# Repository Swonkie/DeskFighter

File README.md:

# DeskFighter

These are the files used to design and build the DeskFighter keyboard.

There is an article which describes the process:

https://haldimann.app/DeskFighter/

## Organization

### 3D Printed Parts

Files in step and 3mf format to 3D print keycaps and other small parts required for the keyboard build.

### FreeCAD

FreeCAD files used to export the 3D printed parts above. If you want to make modifications, this is the most convenient option.

https://www.freecad.org/

### Keycaps Labels

Affinity and svg files used to design the labels. These were imported into FreeCAD.

### Matrix Layout

Spreadsheet used to plan the keyboard matrix layout.

### PCB

KiCad project files used to design the printed circuit board (PCB). The actual manufacturing files (gerber and drill files) are not included, but can be exported from KiCad. Those are then sent to a PCB manufacturer which will make the board.

Also includes the MacroPad files — a test project to figure out some things with a small PCB before ordering the large DeskFighter PCB.

https://www.kicad.org/

## Additional parts required

The mentioned shops are just suggestions. All parts are available in other shops too.

| Shop                                         | Item                                                                                 | Quantity |
| -------------------------------------------- | ------------------------------------------------------------------------------------ | -------: |
| [Keebart](https://www.keebart.com/)          | Switches (Kailh Choc V2 with 2 pins)                                                 |      100 |
|                                              | THT keycaps blank                                                                    |       60 |
|                                              | THT keycaps with dot                                                                 |        2 |
|                                              | THT keycaps with tactile marker                                                      |        2 |
| [Max Gaming](https://www.maxgaming.com/shop) | Durock V3 plate-mounted stabilizer set                                               |        1 |
| [DigiKey](https://www.digikey.com/)          | [Various electronics components](https://www.digikey.com/en/mylists/list/9PG9QW3RYC) |        – |
| [CNC Kitchen](https://cnckitchen.store/)     | M2 heat-set inserts                                                                  |       20 |
|                                              | Installation tip set (optional)                                                      |        1 |
| [AliExpress](https://www.aliexpress.com/)    | M2 × 5 mm screws, black, Torx                                                        |       10 |
|                                              | Rubber feet, 8 mm × 3 mm, self-adhesive                                              |       20 |

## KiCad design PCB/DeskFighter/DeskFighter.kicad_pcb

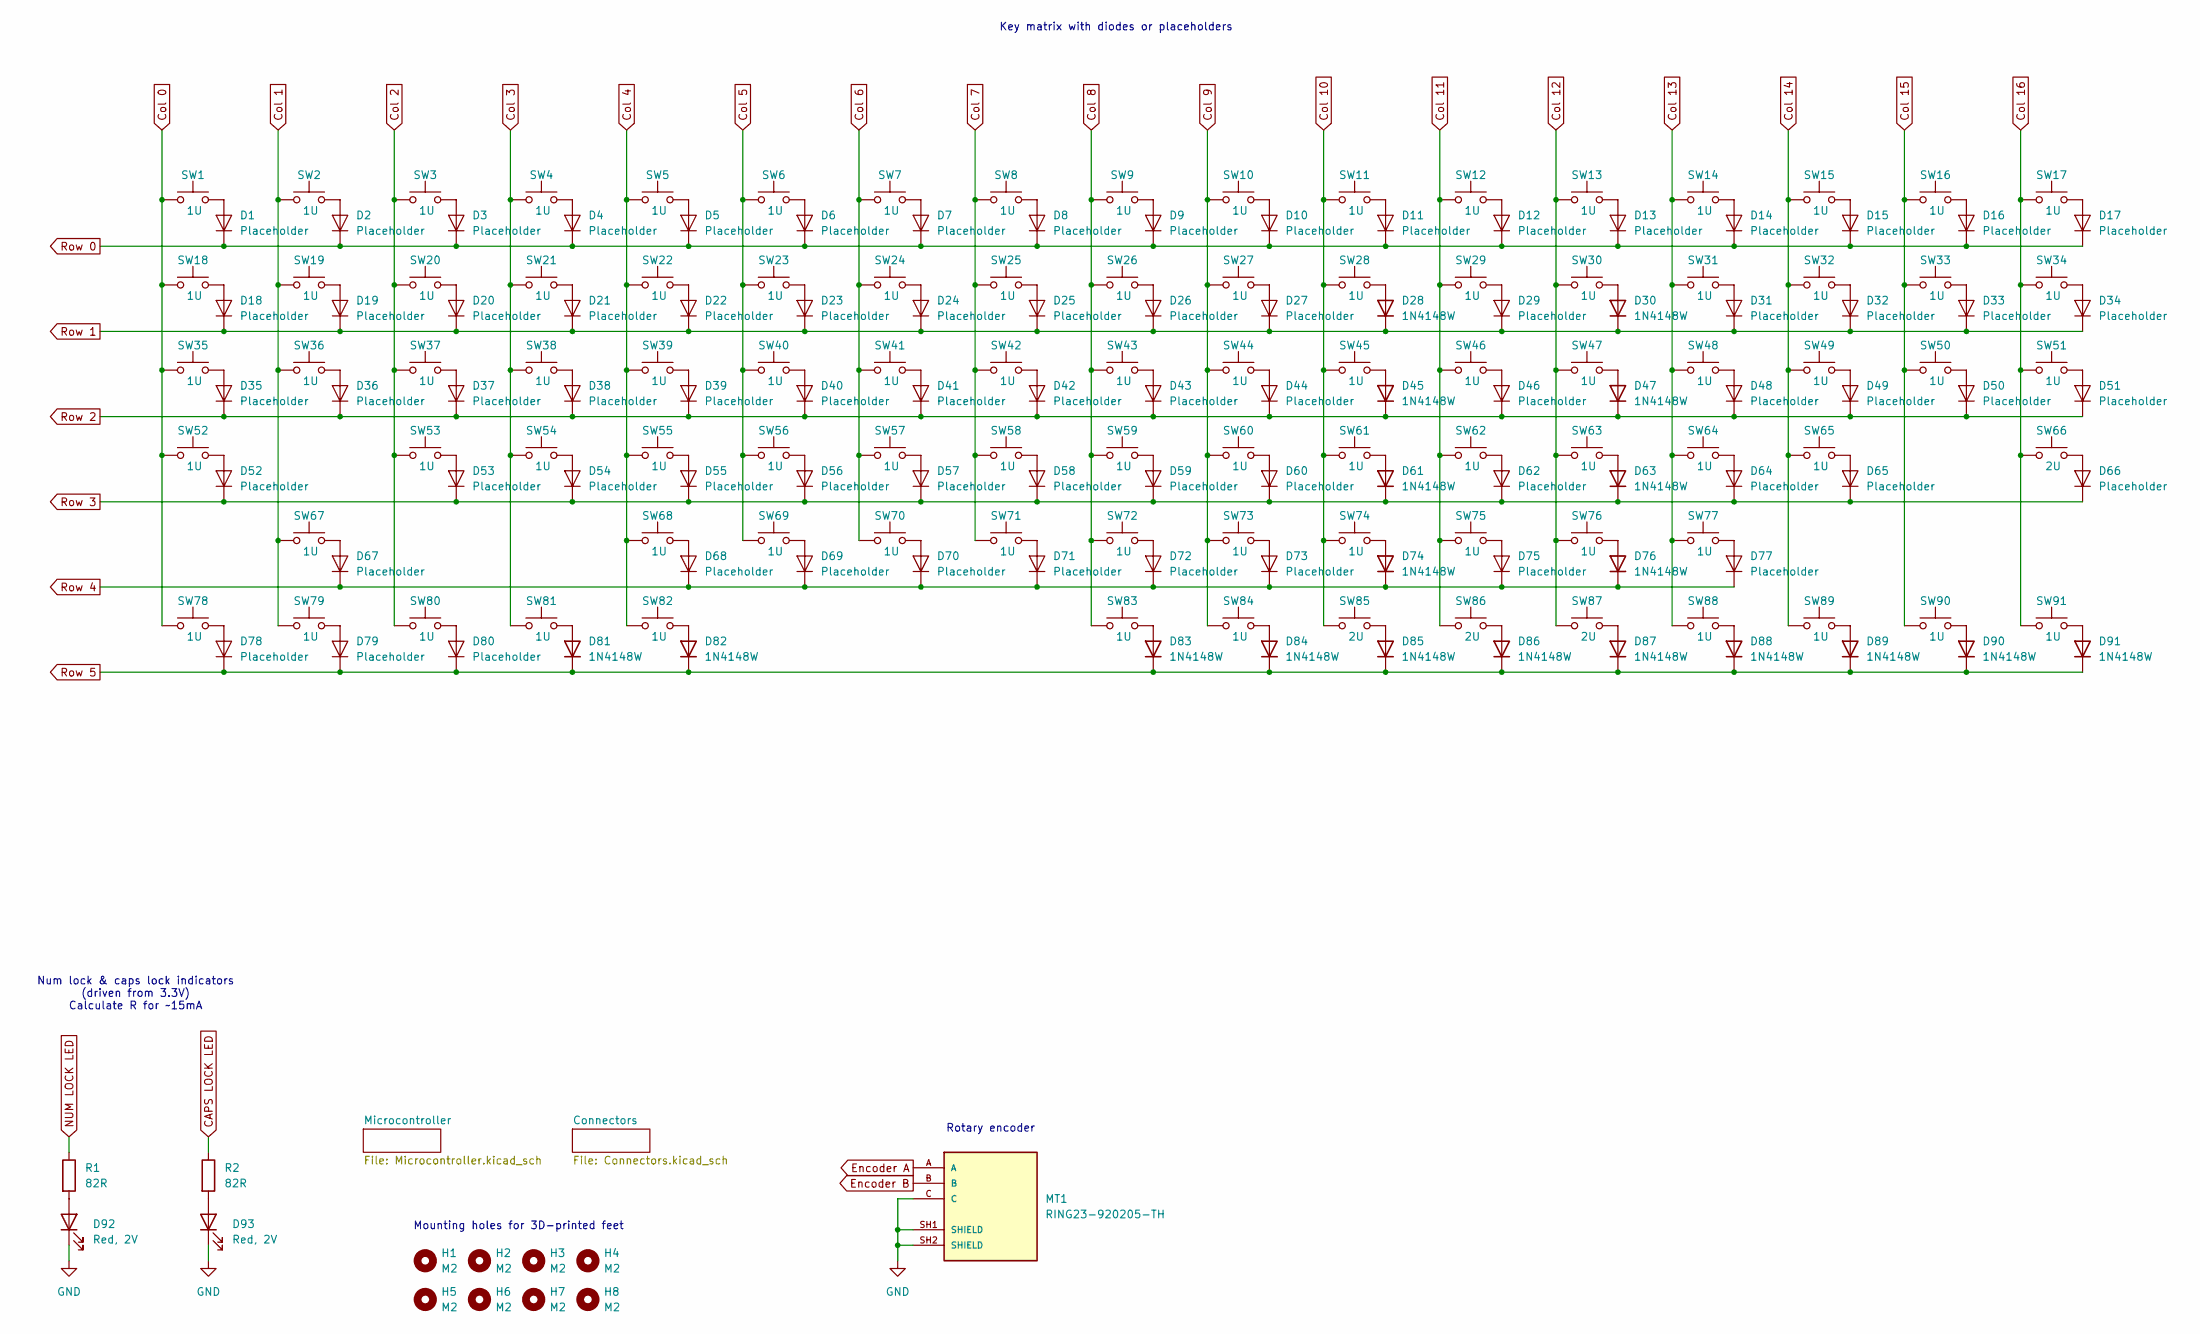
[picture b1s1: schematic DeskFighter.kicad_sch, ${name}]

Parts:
D1, D2, D3, D4, D5, D6, D7, D8, D9, D10, D11, D12, D13, D14, D15, D16, D17, D18, D19, D20, D21, D22, D23, D24, D25, D26, D27, D29, D31, D32, D33, D34, D35, D36, D37, D38, D39, D40, D41, D42, D43, D44, D46, D48, D49, D50, D51, D52, D53, D54, D55, D56, D57, D58, D59, D60, D62, D64, D65, D66, D67, D68, D69, D70, D71, D72, D73, D75, D77, D78, D79, D80: Placeholder; DiodePlaceholder
D28, D30, D45, D47, D61, D63, D74, D76, D81, D82, D83, D84, D85, D86, D87, D88, D89, D90, D91: 1N4148W; D_SOD-123_Handsolder
D92, D93: Red, 2V; LED_0805_2012Metric_Pad1.15x1.40mm_HandSolder
H1, H2, H3, H4, H5, H6, H7, H8: M2; MountingHole_2.2mm_M2_ISO14580_Pad_10mm_Standoffs
MT1: RING23-920205-TH; PARTREV 1.0
R1, R2: 82R; R_0805_2012Metric_Pad1.20x1.40mm_HandSolder
SW1, SW2, SW3, SW4, SW5, SW6, SW7, SW8, SW9, SW10, SW11, SW12, SW13, SW14, SW15, SW16, SW17, SW18, SW19, SW20, SW21, SW22, SW23, SW24, SW25, SW26, SW27, SW28, SW29, SW30, SW31, SW32, SW33, SW34, SW35, SW36, SW37, SW38, SW39, SW40, SW41, SW42, SW43, SW44, SW45, SW46, SW47, SW48, SW49, SW50, SW51, SW52, SW53, SW54, SW55, SW56, SW57, SW58, SW59, SW60, SW61, SW62, SW63, SW64, SW65, SW67, SW68, SW69, SW70, SW71, SW72, SW73, SW74, SW75, SW76, SW77, SW78, SW79, SW80, SW81, SW82, SW83, SW84, SW88, SW89, SW90, SW91: 1U; SW_Kailh_Choc_V2_1.00u
SW66, SW85, SW86, SW87: 2U; SW_Kailh_Choc_V2_2.00u

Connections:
CAPS LOCK LED: R2.1; also elsewhere on the board
Col 0: SW1.1, SW18.1, SW35.1, SW52.1, SW78.1; also elsewhere on the board
Col 1: SW2.1, SW19.1, SW36.1, SW67.1, SW79.1; also elsewhere on the board
Col 2: SW3.1, SW20.1, SW37.1, SW53.1, SW80.1; also elsewhere on the board
Col 3: SW4.1, SW21.1, SW38.1, SW54.1, SW81.1; also elsewhere on the board
Col 4: SW5.1, SW22.1, SW39.1, SW55.1, SW68.1, SW82.1; also elsewhere on the board
Col 5: SW6.1, SW23.1, SW40.1, SW56.1, SW69.1; also elsewhere on the board
Col 6: SW7.1, SW24.1, SW41.1, SW57.1, SW70.1; also elsewhere on the board
Col 7: SW8.1, SW25.1, SW42.1, SW58.1, SW71.1; also elsewhere on the board
Col 8: SW9.1, SW26.1, SW43.1, SW59.1, SW72.1, SW83.1; also elsewhere on the board
Col 9: SW10.1, SW27.1, SW44.1, SW60.1, SW73.1, SW84.1; also elsewhere on the board
Col 10: SW11.1, SW28.1, SW45.1, SW61.1, SW74.1, SW85.1; also elsewhere on the board
Col 11: SW12.1, SW29.1, SW46.1, SW62.1, SW75.1, SW86.1; also elsewhere on the board
Col 12: SW13.1, SW30.1, SW47.1, SW63.1, SW76.1, SW87.1; also elsewhere on the board
Col 13: SW14.1, SW31.1, SW48.1, SW64.1, SW77.1, SW88.1; also elsewhere on the board
Col 14: SW15.1, SW32.1, SW49.1, SW65.1, SW89.1; also elsewhere on the board
Col 15: SW16.1, SW33.1, SW50.1, SW90.1; also elsewhere on the board
Col 16: SW17.1, SW34.1, SW51.1, SW66.1, SW91.1; also elsewhere on the board
Encoder A: MT1.A; also elsewhere on the board
Encoder B: MT1.B; also elsewhere on the board
GND: D92.1 (K), D93.1 (K), MT1.C, MT1.SH1 (SHIELD), MT1.SH2 (SHIELD); also elsewhere on the board
NUM LOCK LED: R1.1; also elsewhere on the board
unnamed: D1.2 (A), SW1.2
unnamed: D2.2 (A), SW2.2
unnamed: D3.2 (A), SW3.2
unnamed: D4.2 (A), SW4.2
unnamed: D5.2 (A), SW5.2
unnamed: D6.2 (A), SW6.2
unnamed: D7.2 (A), SW7.2
unnamed: D8.2 (A), SW8.2
unnamed: D9.2 (A), SW9.2
unnamed: D10.2 (A), SW10.2
unnamed: D11.2 (A), SW11.2
unnamed: D12.2 (A), SW12.2
unnamed: D13.2 (A), SW13.2
unnamed: D14.2 (A), SW14.2
unnamed: D15.2 (A), SW15.2
unnamed: D16.2 (A), SW16.2
unnamed: D17.2 (A), SW17.2
unnamed: D18.2 (A), SW18.2
unnamed: D19.2 (A), SW19.2
unnamed: D20.2 (A), SW20.2
unnamed: D21.2 (A), SW21.2
unnamed: D22.2 (A), SW22.2
unnamed: D23.2 (A), SW23.2
unnamed: D24.2 (A), SW24.2
unnamed: D25.2 (A), SW25.2
unnamed: D26.2 (A), SW26.2
unnamed: D27.2 (A), SW27.2
unnamed: D28.2 (A), SW28.2
unnamed: D29.2 (A), SW29.2
unnamed: D30.2 (A), SW30.2
unnamed: D31.2 (A), SW31.2
unnamed: D32.2 (A), SW32.2
unnamed: D33.2 (A), SW33.2
unnamed: D34.2 (A), SW34.2
unnamed: D35.2 (A), SW35.2
unnamed: D36.2 (A), SW36.2
unnamed: D37.2 (A), SW37.2
unnamed: D38.2 (A), SW38.2
unnamed: D39.2 (A), SW39.2
unnamed: D40.2 (A), SW40.2
unnamed: D41.2 (A), SW41.2
unnamed: D42.2 (A), SW42.2
unnamed: D43.2 (A), SW43.2
unnamed: D44.2 (A), SW44.2
unnamed: D45.2 (A), SW45.2
unnamed: D46.2 (A), SW46.2
unnamed: D47.2 (A), SW47.2
unnamed: D48.2 (A), SW48.2
unnamed: D49.2 (A), SW49.2
unnamed: D50.2 (A), SW50.2
unnamed: D51.2 (A), SW51.2
unnamed: D52.2 (A), SW52.2
unnamed: D53.2 (A), SW53.2
unnamed: D54.2 (A), SW54.2
unnamed: D55.2 (A), SW55.2
unnamed: D56.2 (A), SW56.2
unnamed: D57.2 (A), SW57.2
unnamed: D58.2 (A), SW58.2
unnamed: D59.2 (A), SW59.2
unnamed: D60.2 (A), SW60.2
unnamed: D61.2 (A), SW61.2
unnamed: D62.2 (A), SW62.2
unnamed: D63.2 (A), SW63.2
unnamed: D64.2 (A), SW64.2
unnamed: D65.2 (A), SW65.2
unnamed: D66.2 (A), SW66.2
unnamed: D67.2 (A), SW67.2
unnamed: D68.2 (A), SW68.2
unnamed: D69.2 (A), SW69.2
unnamed: D70.2 (A), SW70.2
unnamed: D71.2 (A), SW71.2
unnamed: D72.2 (A), SW72.2
unnamed: D73.2 (A), SW73.2
unnamed: D74.2 (A), SW74.2
unnamed: D75.2 (A), SW75.2
unnamed: D76.2 (A), SW76.2
unnamed: D77.2 (A), SW77.2
unnamed: D78.2 (A), SW78.2
unnamed: D79.2 (A), SW79.2
unnamed: D80.2 (A), SW80.2
unnamed: D81.2 (A), SW81.2
unnamed: D82.2 (A), SW82.2
unnamed: D83.2 (A), SW83.2
unnamed: D84.2 (A), SW84.2
unnamed: D85.2 (A), SW85.2
unnamed: D86.2 (A), SW86.2
unnamed: D87.2 (A), SW87.2
unnamed: D88.2 (A), SW88.2
unnamed: D89.2 (A), SW89.2
unnamed: D90.2 (A), SW90.2
unnamed: D91.2 (A), SW91.2
unnamed: D92.2 (A), R1.2
unnamed: D93.2 (A), R2.2
Row 0: D1.1 (K), D2.1 (K), D3.1 (K), D4.1 (K), D5.1 (K), D6.1 (K), D7.1 (K), D8.1 (K), D9.1 (K), D10.1 (K), D11.1 (K), D12.1 (K), D13.1 (K), D14.1 (K), D15.1 (K), D16.1 (K), D17.1 (K); also elsewhere on the board
Row 1: D18.1 (K), D19.1 (K), D20.1 (K), D21.1 (K), D22.1 (K), D23.1 (K), D24.1 (K), D25.1 (K), D26.1 (K), D27.1 (K), D28.1 (K), D29.1 (K), D30.1 (K), D31.1 (K), D32.1 (K), D33.1 (K), D34.1 (K); also elsewhere on the board
Row 2: D35.1 (K), D36.1 (K), D37.1 (K), D38.1 (K), D39.1 (K), D40.1 (K), D41.1 (K), D42.1 (K), D43.1 (K), D44.1 (K), D45.1 (K), D46.1 (K), D47.1 (K), D48.1 (K), D49.1 (K), D50.1 (K), D51.1 (K); also elsewhere on the board
Row 3: D52.1 (K), D53.1 (K), D54.1 (K), D55.1 (K), D56.1 (K), D57.1 (K), D58.1 (K), D59.1 (K), D60.1 (K), D61.1 (K), D62.1 (K), D63.1 (K), D64.1 (K), D65.1 (K), D66.1 (K); also elsewhere on the board
Row 4: D67.1 (K), D68.1 (K), D69.1 (K), D70.1 (K), D71.1 (K), D72.1 (K), D73.1 (K), D74.1 (K), D75.1 (K), D76.1 (K), D77.1 (K); also elsewhere on the board
Row 5: D78.1 (K), D79.1 (K), D80.1 (K), D81.1 (K), D82.1 (K), D83.1 (K), D84.1 (K), D85.1 (K), D86.1 (K), D87.1 (K), D88.1 (K), D89.1 (K), D90.1 (K), D91.1 (K); also elsewhere on the board

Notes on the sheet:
Key matrix with diodes or placeholders
Rotary encoder
Mounting holes for 3D-printed feet
Num lock & caps lock indicators (driven from 3.3V) Calculate R for ~15mA

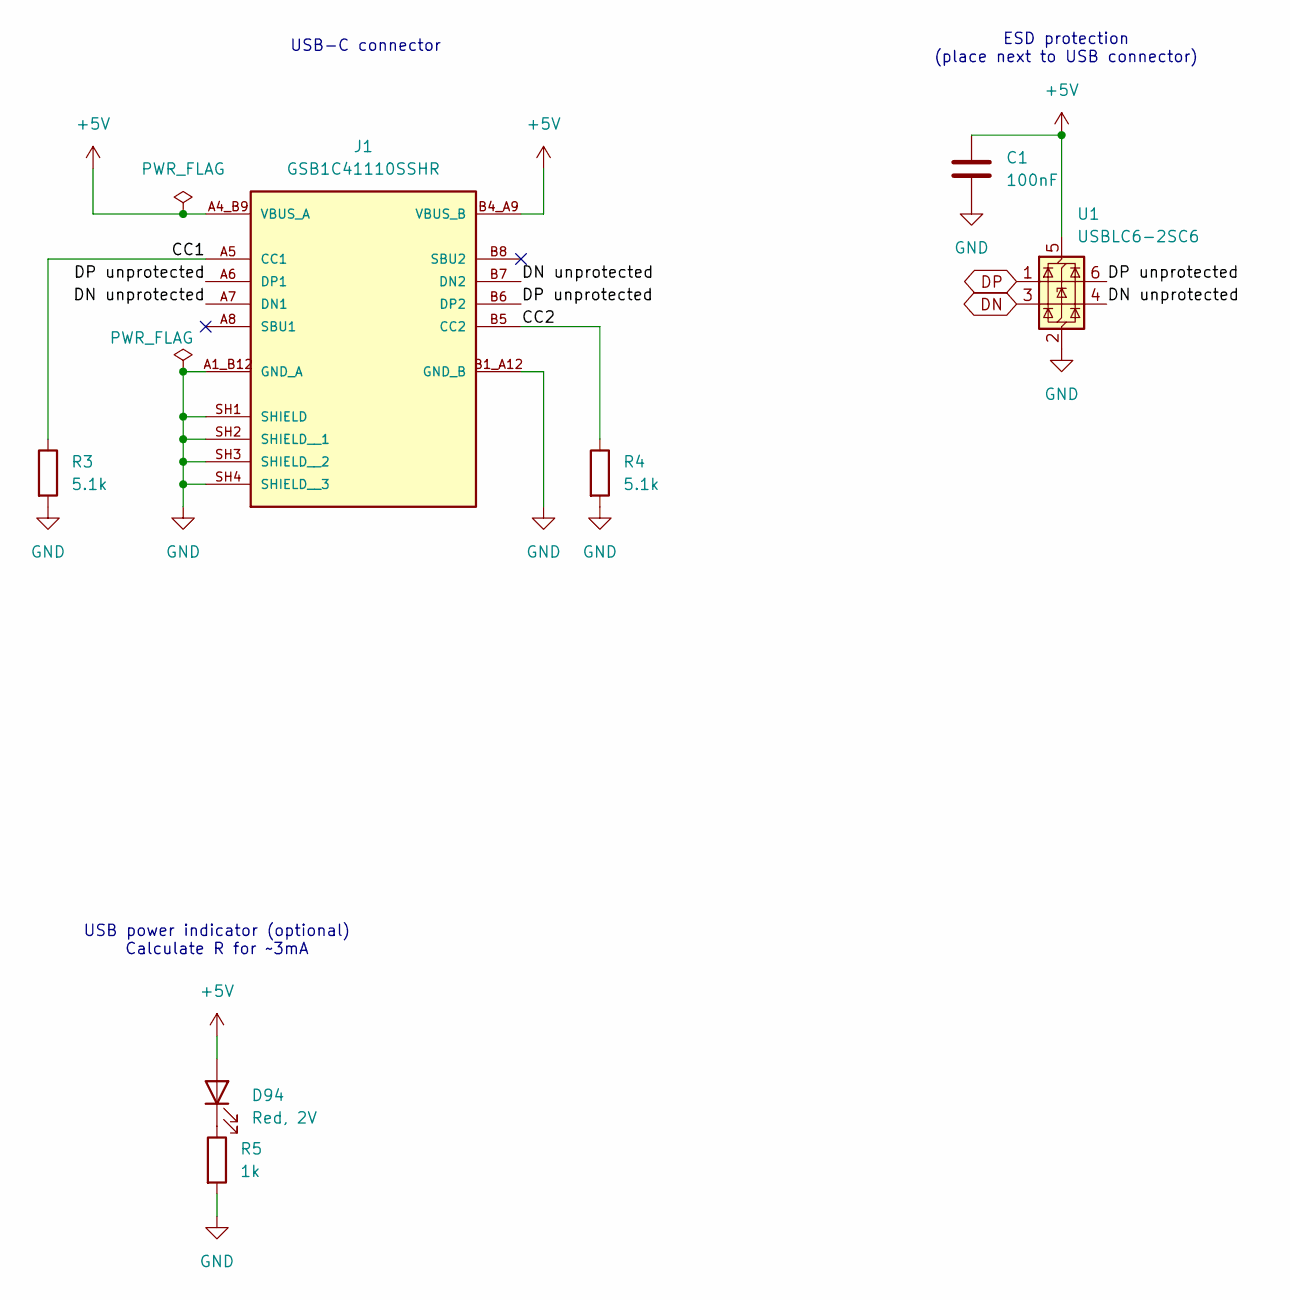
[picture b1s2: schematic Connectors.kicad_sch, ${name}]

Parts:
C1: 100nF; C_0805_2012Metric_Pad1.18x1.45mm_HandSolder
D94: Red, 2V; LED_0805_2012Metric_Pad1.15x1.40mm_HandSolder
J1: GSB1C41110SSHR; AMPHENOL_GSB1C41110SSHR; PARTREV AX1
R3, R4: 5.1k; R_0805_2012Metric_Pad1.20x1.40mm_HandSolder
R5: 1k; R_0805_2012Metric_Pad1.20x1.40mm_HandSolder
U1: USBLC6-2SC6; SOT-23-6_Handsoldering

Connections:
+5V: C1.1, D94.2 (A), J1.A4_B9 (VBUS_A), J1.B4_A9 (VBUS_B), U1.5 (VBUS); also elsewhere on the board
/Connectors/CC1: J1.A5 (CC1), R3.1
/Connectors/CC2: J1.B5 (CC2), R4.1
/Connectors/DN unprotected: J1.A7 (DN1), J1.B7 (DN2), U1.4 (I/O2)
/Connectors/DP unprotected: J1.A6 (DP1), J1.B6 (DP2), U1.6 (I/O1)
DN: U1.3 (I/O2); also elsewhere on the board
DP: U1.1 (I/O1); also elsewhere on the board
GND: C1.2, J1.A1_B12 (GND_A), J1.B1_A12 (GND_B), J1.SH1 (SHIELD), J1.SH2 (SHIELD__1), J1.SH3 (SHIELD__2), J1.SH4 (SHIELD__3), R3.2, R4.2, R5.2, U1.2 (GND); also elsewhere on the board
unnamed: D94.1 (K), R5.1

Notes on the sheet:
USB power indicator (optional) Calculate R for ~3mA
ESD protection (place next to USB connector)
USB-C connector

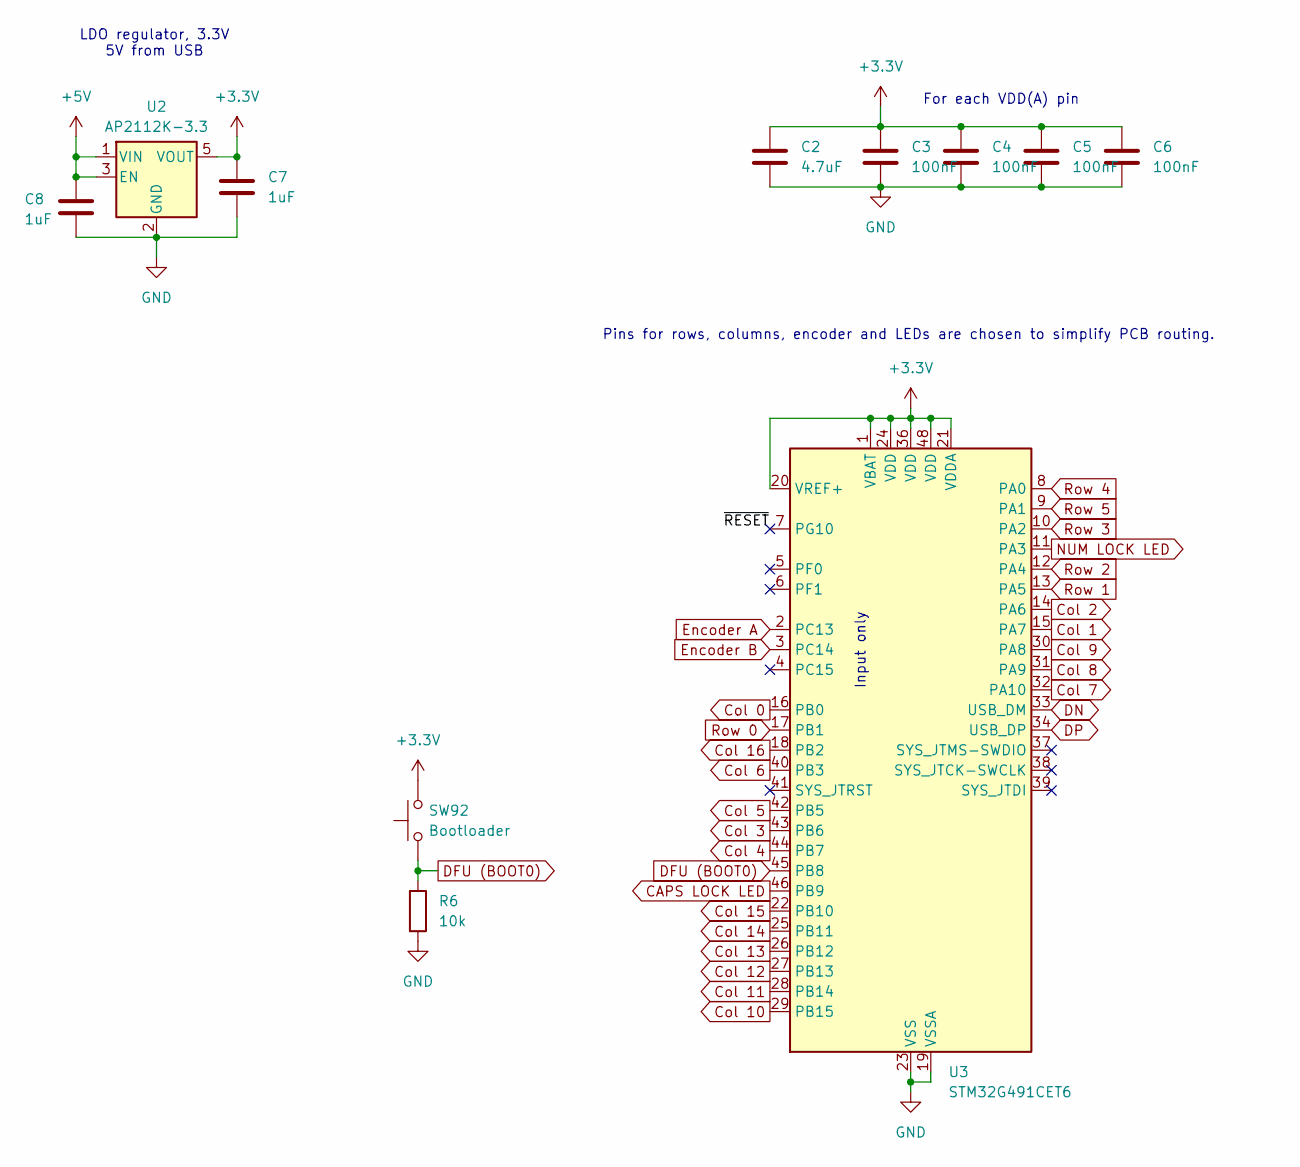
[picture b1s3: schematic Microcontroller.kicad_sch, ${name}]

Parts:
C2: 4.7uF; C_0805_2012Metric_Pad1.18x1.45mm_HandSolder
C3, C4, C5, C6: 100nF; C_0805_2012Metric_Pad1.18x1.45mm_HandSolder
C7, C8: 1uF; C_0805_2012Metric_Pad1.18x1.45mm_HandSolder
R6: 10k; R_0805_2012Metric_Pad1.20x1.40mm_HandSolder
SW92: Bootloader; SW_SPST_PTS645Sx43SMTR92
U2: AP2112K-3.3; SOT-23-5_HandSoldering
U3: STM32G491CET6; LQFP-48_7x7mm_P0.5mm

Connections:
+3.3V: C2.1, C3.1, C4.1, C5.1, C6.1, C7.1, SW92.2, U2.5 (VOUT), U3.1 (VBAT), U3.20 (VREF+), U3.21 (VDDA), U3.24 (VDD), U3.36 (VDD), U3.48 (VDD)
+5V: C8.1, U2.1 (VIN), U2.3 (EN); also elsewhere on the board
/Microcontroller/~RESET: U3.7 (PG10)
CAPS LOCK LED: U3.46 (PB9); also elsewhere on the board
Col 0: U3.16 (PB0); also elsewhere on the board
Col 1: U3.15 (PA7); also elsewhere on the board
Col 2: U3.14 (PA6); also elsewhere on the board
Col 3: U3.43 (PB6); also elsewhere on the board
Col 4: U3.44 (PB7); also elsewhere on the board
Col 5: U3.42 (PB5); also elsewhere on the board
Col 6: U3.40 (PB3); also elsewhere on the board
Col 7: U3.32 (PA10); also elsewhere on the board
Col 8: U3.31 (PA9); also elsewhere on the board
Col 9: U3.30 (PA8); also elsewhere on the board
Col 10: U3.29 (PB15); also elsewhere on the board
Col 11: U3.28 (PB14); also elsewhere on the board
Col 12: U3.27 (PB13); also elsewhere on the board
Col 13: U3.26 (PB12); also elsewhere on the board
Col 14: U3.25 (PB11); also elsewhere on the board
Col 15: U3.22 (PB10); also elsewhere on the board
Col 16: U3.18 (PB2); also elsewhere on the board
DFU (BOOT0): R6.1, SW92.1, U3.45 (PB8)
DN: U3.33 (USB_DM); also elsewhere on the board
DP: U3.34 (USB_DP); also elsewhere on the board
Encoder A: U3.2 (PC13); also elsewhere on the board
Encoder B: U3.3 (PC14); also elsewhere on the board
GND: C2.2, C3.2, C4.2, C5.2, C6.2, C7.2, C8.2, R6.2, U2.2 (GND), U3.19 (VSSA), U3.23 (VSS), U3.35 (VSS), U3.47 (VSS); also elsewhere on the board
NUM LOCK LED: U3.11 (PA3); also elsewhere on the board
Row 0: U3.17 (PB1); also elsewhere on the board
Row 1: U3.13 (PA5); also elsewhere on the board
Row 2: U3.12 (PA4); also elsewhere on the board
Row 3: U3.10 (PA2); also elsewhere on the board
Row 4: U3.8 (PA0); also elsewhere on the board
Row 5: U3.9 (PA1); also elsewhere on the board

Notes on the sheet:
Pins for rows, columns, encoder and LEDs are chosen to simplify PCB routing.
Input only
LDO regulator, 3.3V 5V from USB
For each VDD(A) pin

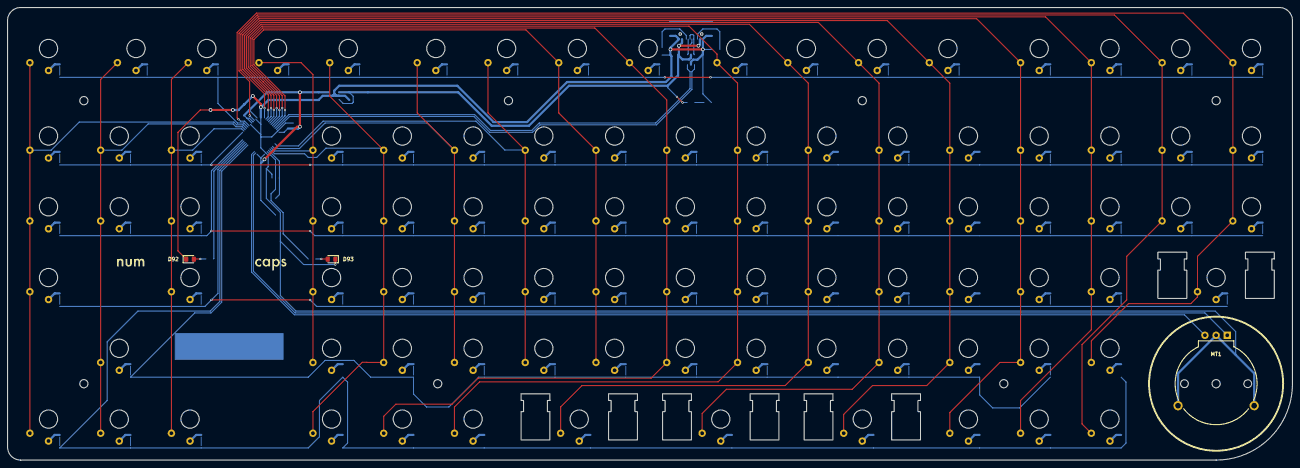
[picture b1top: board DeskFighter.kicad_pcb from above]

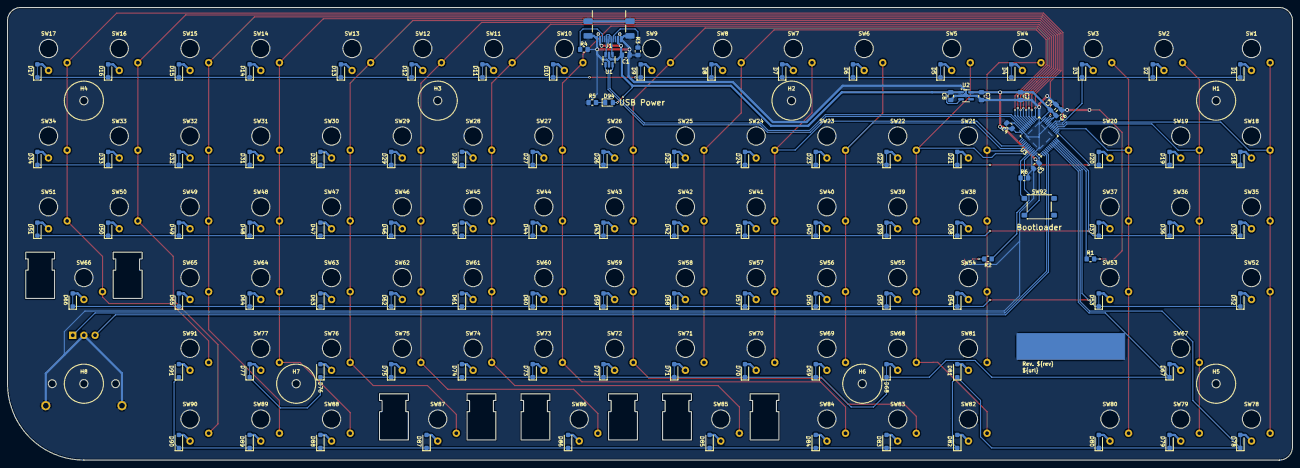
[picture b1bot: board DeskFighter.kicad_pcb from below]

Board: 2 copper layers, 345.0 x 121.5 mm, 213 parts (111 on the bottom side), 131 nets.

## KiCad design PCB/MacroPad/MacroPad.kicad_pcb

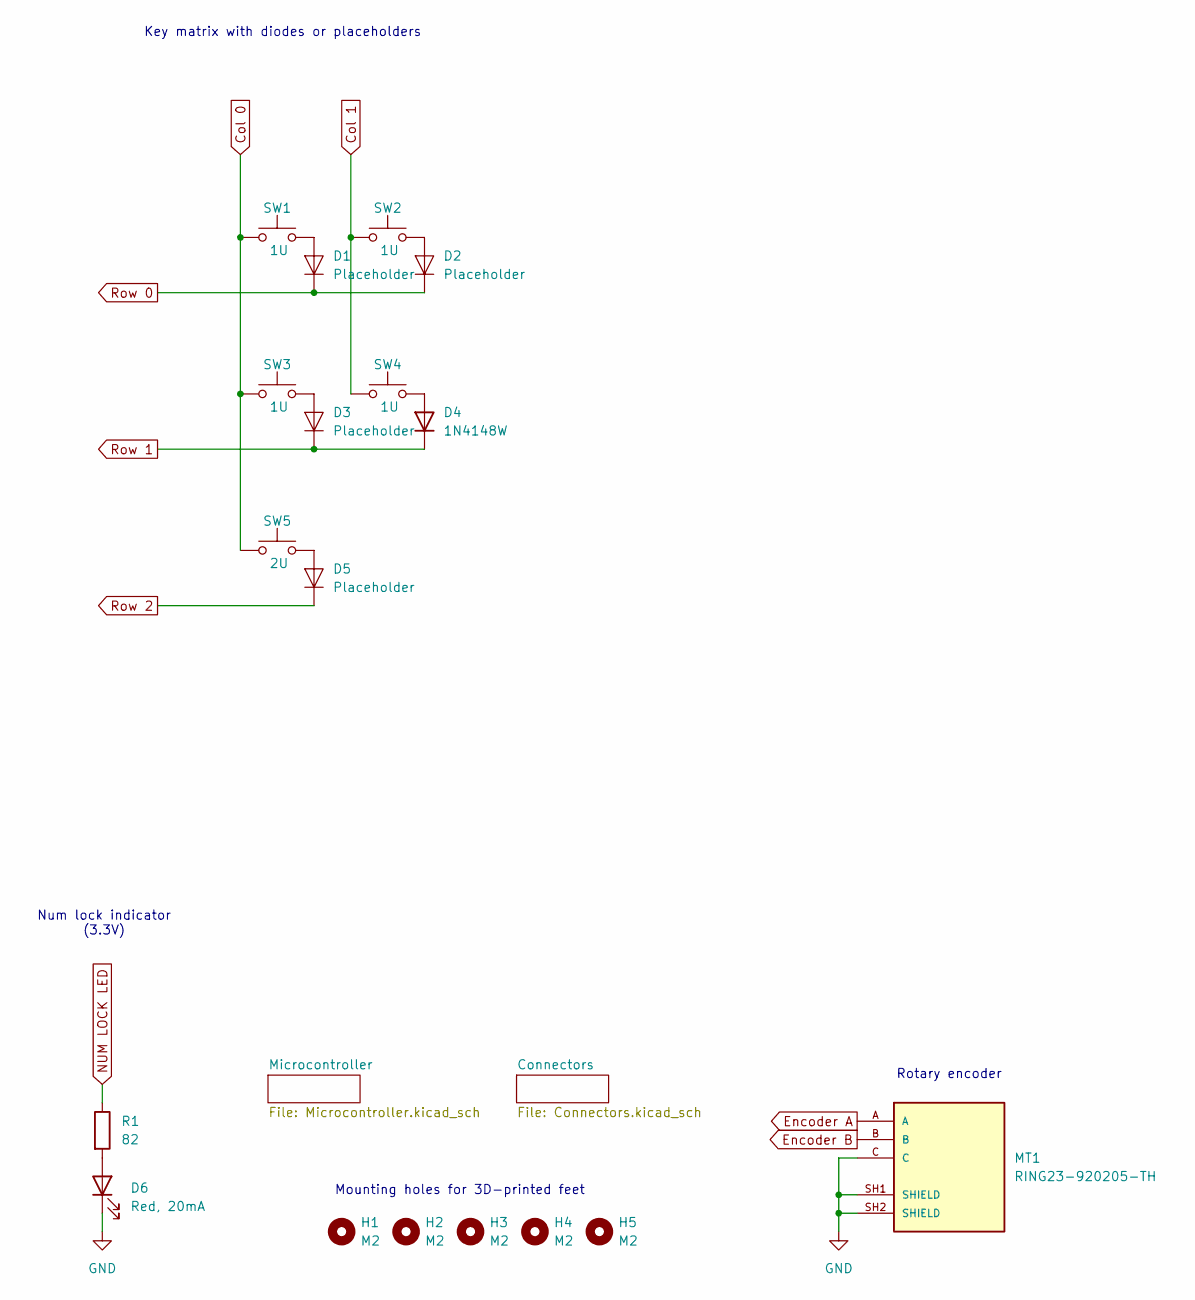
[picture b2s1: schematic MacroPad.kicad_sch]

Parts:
D1, D2, D3, D5: Placeholder; DiodePlaceholder
D4: 1N4148W; D_SOD-123_Handsolder; LCSC Part # C2099
D6: Red, 20mA; LED_0805_2012Metric_Pad1.15x1.40mm_HandSolder; LCSC Part # C2295
H1, H2, H3, H4, H5: M2; MountingHole_2.2mm_M2_ISO14580_Pad_10mm_Standoffs
MT1: RING23-920205-TH; PARTREV 1.0
R1: 82; R_0805_2012Metric_Pad1.20x1.40mm_HandSolder
SW1, SW2, SW3, SW4: 1U; SW_Kailh_Choc_V2_1.00u
SW5: 2U; SW_Kailh_Choc_V2_2.00u

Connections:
Col 0: SW1.1, SW3.1, SW5.1; also elsewhere on the board
Col 1: SW2.1, SW4.1; also elsewhere on the board
Encoder A: MT1.A; also elsewhere on the board
Encoder B: MT1.B; also elsewhere on the board
GND: D6.1 (K), MT1.C, MT1.SH1 (SHIELD), MT1.SH2 (SHIELD); also elsewhere on the board
NUM LOCK LED: R1.1; also elsewhere on the board
unnamed: D1.2 (A), SW1.2
unnamed: D2.2 (A), SW2.2
unnamed: D3.2 (A), SW3.2
unnamed: D4.2 (A), SW4.2
unnamed: D5.2 (A), SW5.2
unnamed: D6.2 (A), R1.2
Row 0: D1.1 (K), D2.1 (K); also elsewhere on the board
Row 1: D3.1 (K), D4.1 (K); also elsewhere on the board
Row 2: D5.1 (K); also elsewhere on the board

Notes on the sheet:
Key matrix with diodes or placeholders
Rotary encoder
Mounting holes for 3D-printed feet
Num lock indicator (3.3V)

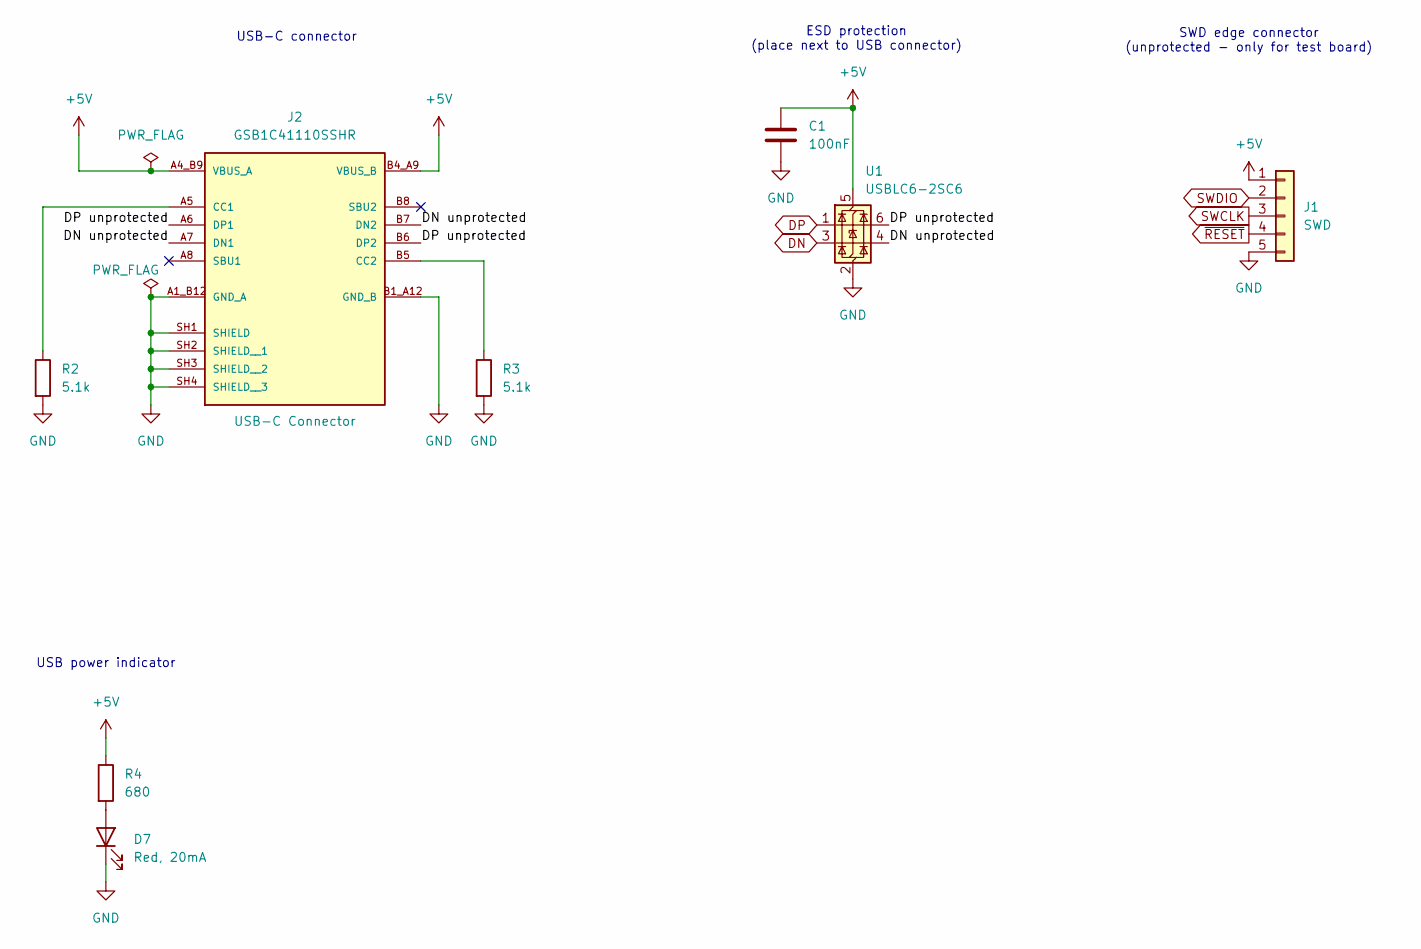
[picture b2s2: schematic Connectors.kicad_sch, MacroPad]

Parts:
C1: 100nF; C_0805_2012Metric_Pad1.18x1.45mm_HandSolder; LCSC Part # C1711
D7: Red, 20mA; LED_0805_2012Metric_Pad1.15x1.40mm_HandSolder; LCSC Part # C2295
J1: SWD; SWD_Programming_Edge_Connector_Single
J2: GSB1C41110SSHR; AMPHENOL_GSB1C41110SSHR; PARTREV AX1; LCSC Part # C34260841
R2, R3: 5.1k; R_0805_2012Metric_Pad1.20x1.40mm_HandSolder
R4: 680; R_0805_2012Metric_Pad1.20x1.40mm_HandSolder
U1: USBLC6-2SC6; SOT-23-6_Handsoldering; LCSC Part # C7519

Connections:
+5V: C1.1, J1.1, J2.A4_B9 (VBUS_A), J2.B4_A9 (VBUS_B), R4.1, U1.5 (VBUS); also elsewhere on the board
/Connectors/DN unprotected: J2.A7 (DN1), J2.B7 (DN2), U1.4 (I/O2)
/Connectors/DP unprotected: J2.A6 (DP1), J2.B6 (DP2), U1.6 (I/O1)
DN: U1.3 (I/O2); also elsewhere on the board
DP: U1.1 (I/O1); also elsewhere on the board
GND: C1.2, D7.1 (K), J1.5, J2.A1_B12 (GND_A), J2.B1_A12 (GND_B), J2.SH1 (SHIELD), J2.SH2 (SHIELD__1), J2.SH3 (SHIELD__2), J2.SH4 (SHIELD__3), R2.2, R3.2, U1.2 (GND); also elsewhere on the board
unnamed: D7.2 (A), R4.2
unnamed: J2.A5 (CC1), R2.1
unnamed: J2.B5 (CC2), R3.1
SWCLK: J1.3; also elsewhere on the board
SWDIO: J1.2; also elsewhere on the board
~RESET: J1.4; also elsewhere on the board

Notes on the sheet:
SWD edge connector (unprotected - only for test board)
USB power indicator
ESD protection (place next to USB connector)
USB-C connector

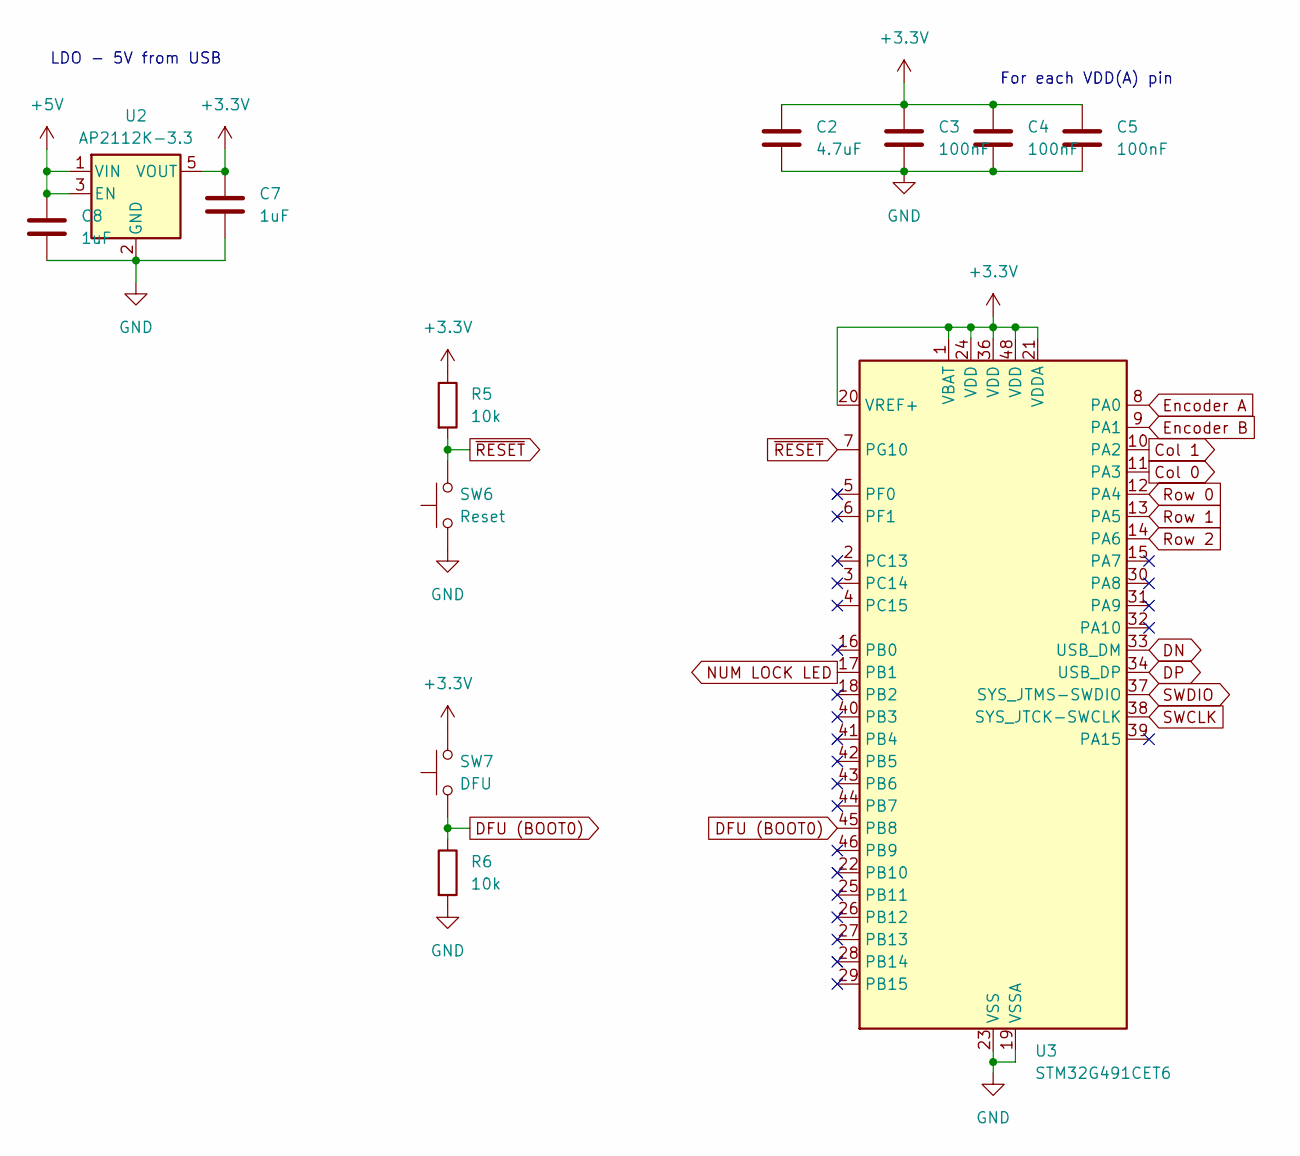
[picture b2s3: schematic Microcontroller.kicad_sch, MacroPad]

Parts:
C2: 4.7uF; C_0805_2012Metric_Pad1.18x1.45mm_HandSolder; LCSC Part # C1746
C3, C4, C5: 100nF; C_0805_2012Metric_Pad1.18x1.45mm_HandSolder; LCSC Part # C1711
C7, C8: 1uF; C_0805_2012Metric_Pad1.18x1.45mm_HandSolder; LCSC Part # C1712
R5, R6: 10k; R_0805_2012Metric_Pad1.20x1.40mm_HandSolder
SW6: Reset; SW_SPST_PTS645Sx43SMTR92
SW7: DFU; SW_SPST_PTS645Sx43SMTR92
U2: AP2112K-3.3; SOT-23-5_HandSoldering; LCSC Part # C23380830
U3: STM32G491CET6; LQFP-48_7x7mm_P0.5mm; LCSC Part # C3227300

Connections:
+3.3V: C2.1, C3.1, C4.1, C5.1, C7.1, R5.1, SW7.2, U2.5 (VOUT), U3.1 (VBAT), U3.20 (VREF+), U3.21 (VDDA), U3.24 (VDD), U3.36 (VDD), U3.48 (VDD)
+5V: C8.1, U2.1 (VIN), U2.3 (EN); also elsewhere on the board
Col 0: U3.11 (PA3); also elsewhere on the board
Col 1: U3.10 (PA2); also elsewhere on the board
DFU (BOOT0): R6.1, SW7.1, U3.45 (PB8)
DN: U3.33 (USB_DM); also elsewhere on the board
DP: U3.34 (USB_DP); also elsewhere on the board
Encoder A: U3.8 (PA0); also elsewhere on the board
Encoder B: U3.9 (PA1); also elsewhere on the board
GND: C2.2, C3.2, C4.2, C5.2, C7.2, C8.2, R6.2, SW6.1, U2.2 (GND), U3.19 (VSSA), U3.23 (VSS), U3.35 (VSS), U3.47 (VSS); also elsewhere on the board
NUM LOCK LED: U3.17 (PB1); also elsewhere on the board
Row 0: U3.12 (PA4); also elsewhere on the board
Row 1: U3.13 (PA5); also elsewhere on the board
Row 2: U3.14 (PA6); also elsewhere on the board
SWCLK: U3.38 (SYS_JTCK-SWCLK); also elsewhere on the board
SWDIO: U3.37 (SYS_JTMS-SWDIO); also elsewhere on the board
~RESET: R5.2, SW6.2, U3.7 (PG10); also elsewhere on the board

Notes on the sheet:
LDO - 5V from USB
For each VDD(A) pin

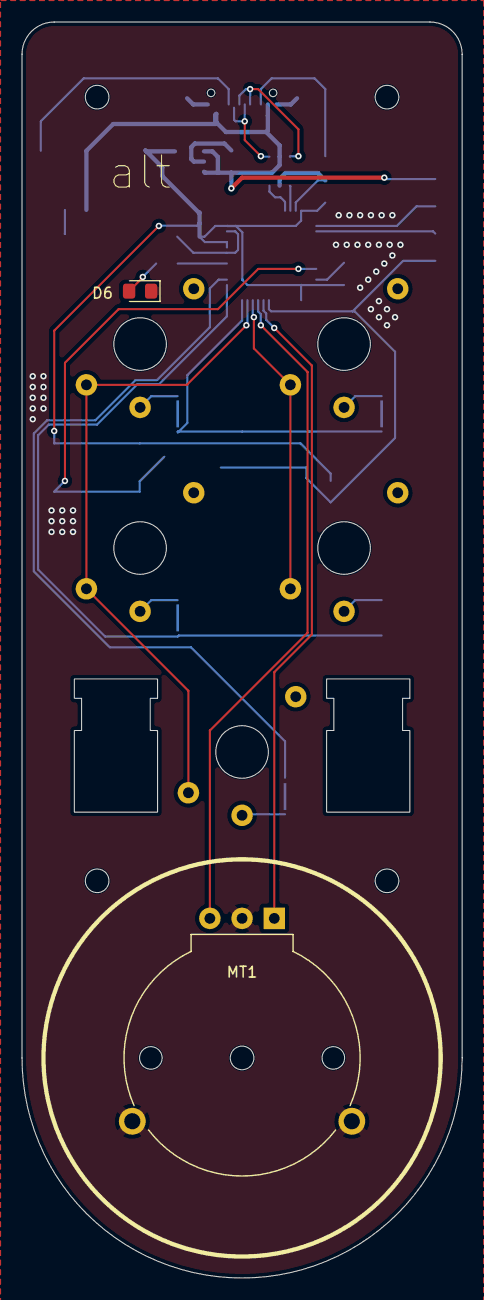
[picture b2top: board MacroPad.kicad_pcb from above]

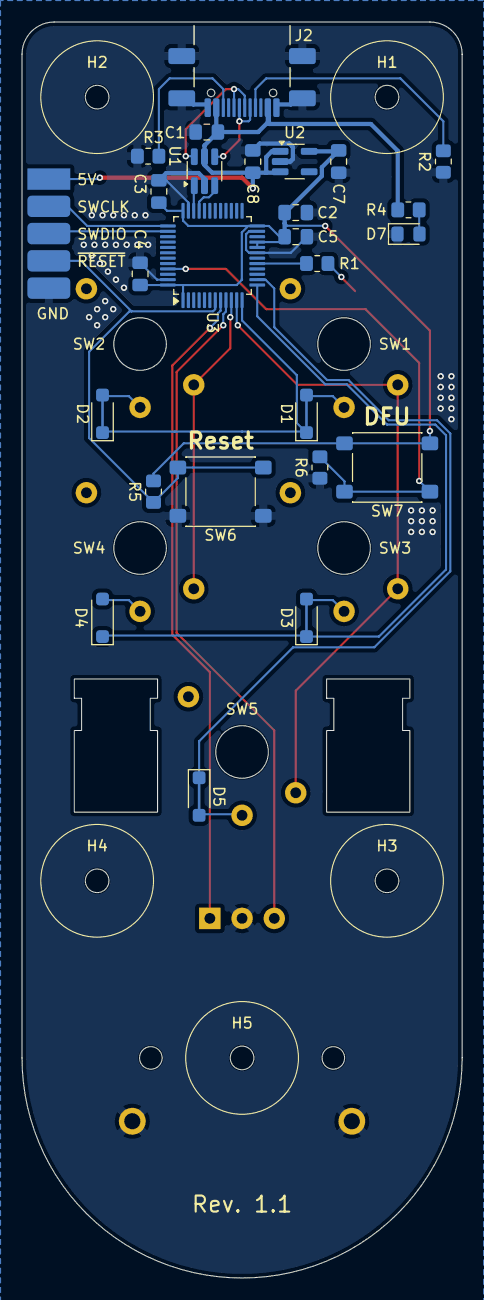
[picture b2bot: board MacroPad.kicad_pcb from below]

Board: 2 copper layers, 41.0 x 117.0 mm, 38 parts (26 on the bottom side), 28 nets.
